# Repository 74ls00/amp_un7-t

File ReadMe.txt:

Проект EAGLE 6.4
Стандартные библиотеки https://github.com/74ls00/eagle6_lbr_sort
Мои библиотеки https://github.com/74ls00/eagle6_mylbr
  отсутствующие стандартные библиотеки изменены и расположены по новому пути https://github.com/74ls00/eagle6_mylbr/tree/master/EAGLE%20mod

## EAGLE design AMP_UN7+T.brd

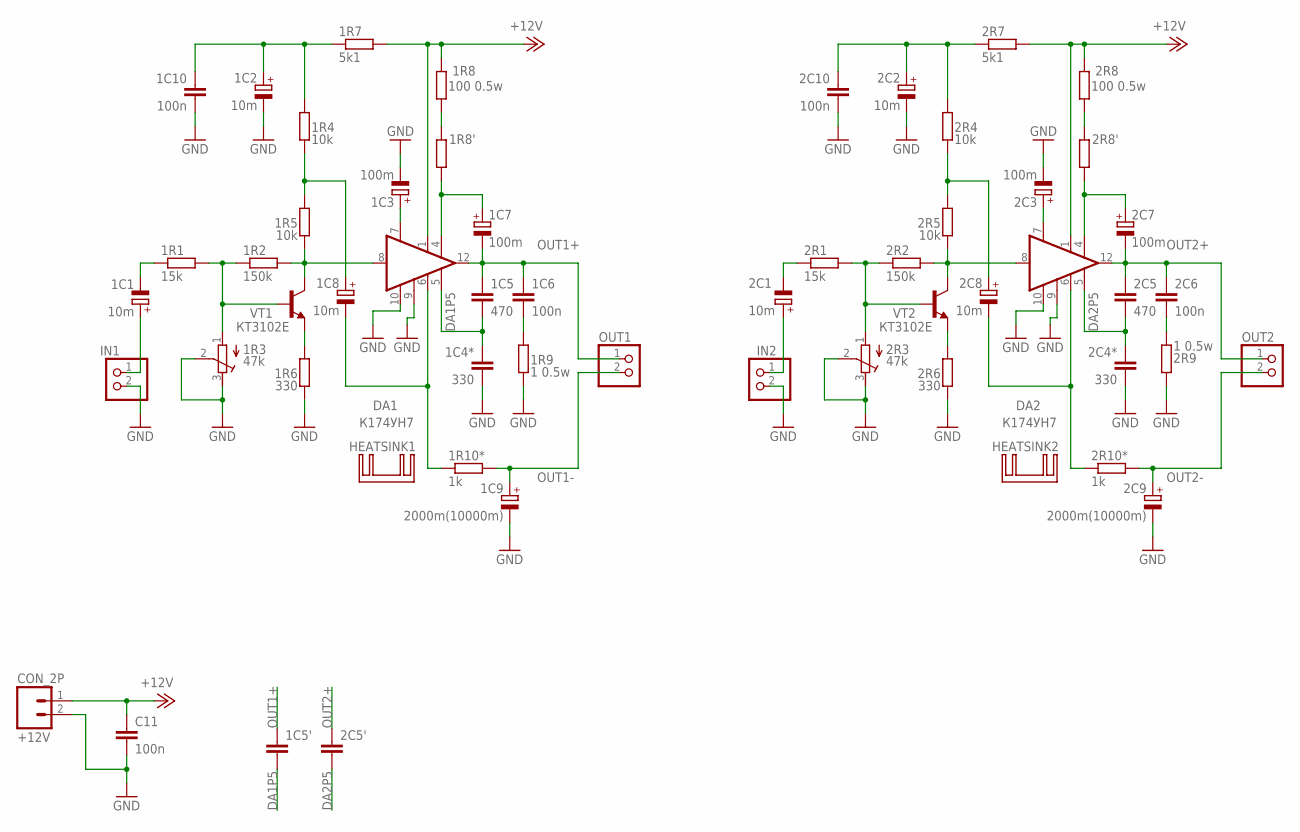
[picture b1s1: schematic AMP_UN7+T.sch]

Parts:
1C1, 1C2, 1C8, 2C1, 2C2, 2C8: 10m; E2,5-5
1C3, 2C3: 100m; E2,5-6
1C4*, 2C4*: 330; C050-025X075
1C5, 2C5: 470; C050-030X075
1C5', 2C5': C-EUC0805; C0805
1C6, 2C6: 100n; C075-052X106
1C7, 2C7: 100m; E2,5-5
1C9, 2C9: 2000m(10000m); E5-13
1C10, 2C10: 100n; C0805
1R1, 2R1: 15k; R0805
1R2, 2R2: 150k; R0805
1R3, 2R3: 47k; RTRIM3296W
1R4, 1R5, 2R4, 2R5: 10k; R0805
1R6, 2R6: 330; R0805
1R7, 2R7: 5k1; R0805
1R8, 2R8: 100 0.5w; R1210W
1R8', 2R8': R-EU_R1210W; R1210W
1R9, 2R9: 1 0.5w; 0411V
1R10*, 2R10*: 1k; 0207/12
+12V: CON_2P; CON_PWR_2PIN4MM
C11: 100n; C0805
DA1, DA2: К174УН7; DIL16-12
HEATSINK1, HEATSINK2: HEATSINK_V; H_VELS
IN1, IN2: PINHD-1X2; 1X02
OUT1, OUT2: PINHD-1X2; 1X02
VT1, VT2: КТ3102Е; TO92

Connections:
+12V: 1R7.2, 1R8.2, 2R7.2, 2R8.2, +12V.1, C11.1, DA1.1 (1+V), DA2.1 (1+V)
DA1P5: 1C4*.1, 1C5.2, 1C5'.2, DA1.5 (5KOR)
DA2P5: 2C4*.1, 2C5.2, 2C5'.2, DA2.5 (5KOR)
GND: 1C2.-, 1C3.-, 1C4*.2, 1C9.-, 1C10.2, 1R3.2 (S), 1R3.3 (E), 1R6.1, 1R9.1, 2C2.-, 2C3.-, 2C4*.2, 2C9.-, 2C10.2, 2R3.2 (S), 2R3.3 (E), 2R6.1, 2R9.2, +12V.2, C11.2, DA1.9 (9-V), DA1.10 (10E), DA2.9 (9-V), DA2.10 (10E), IN1.2, IN2.2
IN1: 1C1.+, IN1.1
IN2: 2C1.+, IN2.1
unnamed: 1R2.2, 1R5.1, DA1.8 (8IN), VT1.1 (C)
unnamed: 1R6.2, VT1.3 (E)
unnamed: 1R1.2, 1R2.1, 1R3.1 (A), VT1.2 (B)
unnamed: 1C1.-, 1R1.1
unnamed: 1C8.+, 1R4.1, 1R5.2
unnamed: 1C2.+, 1C10.1, 1R4.2, 1R7.1
unnamed: 1C3.+, DA1.7 (7FILTR)
unnamed: 1C7.+, 1R8'.1, DA1.4 (4++U)
unnamed: 1R8.1, 1R8'.2
unnamed: 1C6.2, 1R9.2
unnamed: 1C8.-, 1R10*.1, DA1.6 (6FB)
unnamed: 2R2.2, 2R5.1, DA2.8 (8IN), VT2.1 (C)
unnamed: 2R6.2, VT2.3 (E)
unnamed: 2R1.2, 2R2.1, 2R3.1 (A), VT2.2 (B)
unnamed: 2C1.-, 2R1.1
unnamed: 2C8.+, 2R4.1, 2R5.2
unnamed: 2C2.+, 2C10.1, 2R4.2, 2R7.1
unnamed: 2C3.+, DA2.7 (7FILTR)
unnamed: 2C7.+, 2R8'.1, DA2.4 (4++U)
unnamed: 2C6.2, 2R9.1
unnamed: 2C8.-, 2R10*.1, DA2.6 (6FB)
unnamed: 2R8.1, 2R8'.2
OUT1+: 1C5.1, 1C5'.1, 1C6.1, 1C7.-, DA1.12 (12OUT), OUT1.1
OUT1-: 1C9.+, 1R10*.2, OUT1.2
OUT2+: 2C5.1, 2C5'.1, 2C6.1, 2C7.-, DA2.12 (12OUT), OUT2.1
OUT2-: 2C9.+, 2R10*.2, OUT2.2

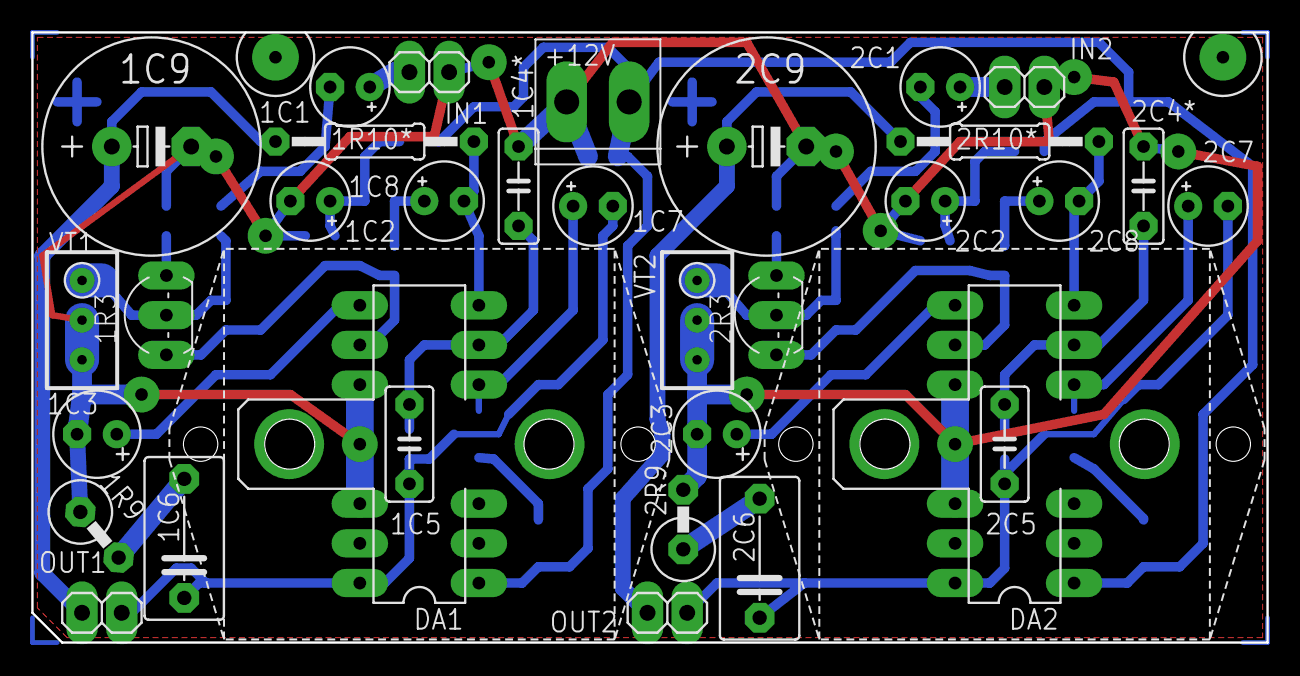
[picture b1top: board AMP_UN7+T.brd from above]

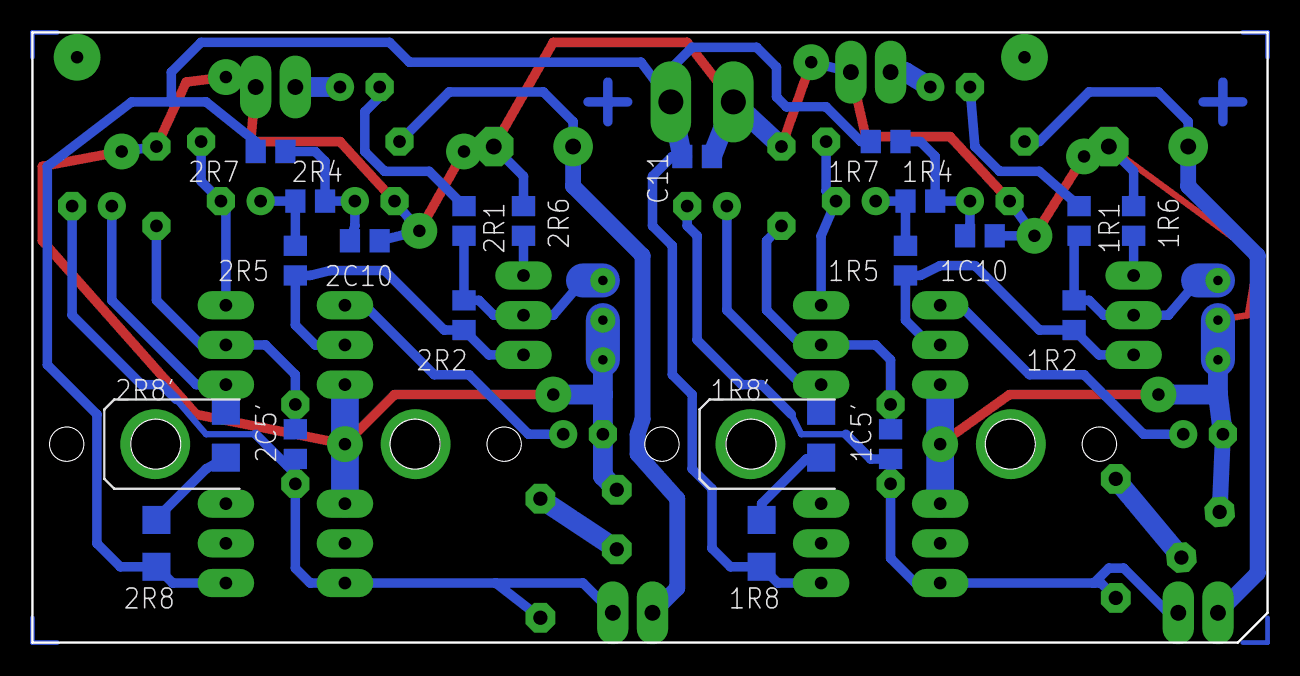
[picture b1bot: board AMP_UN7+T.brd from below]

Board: 2 copper layers, 79.1 x 39.1 mm, 56 parts (21 on the bottom side), 32 nets.
